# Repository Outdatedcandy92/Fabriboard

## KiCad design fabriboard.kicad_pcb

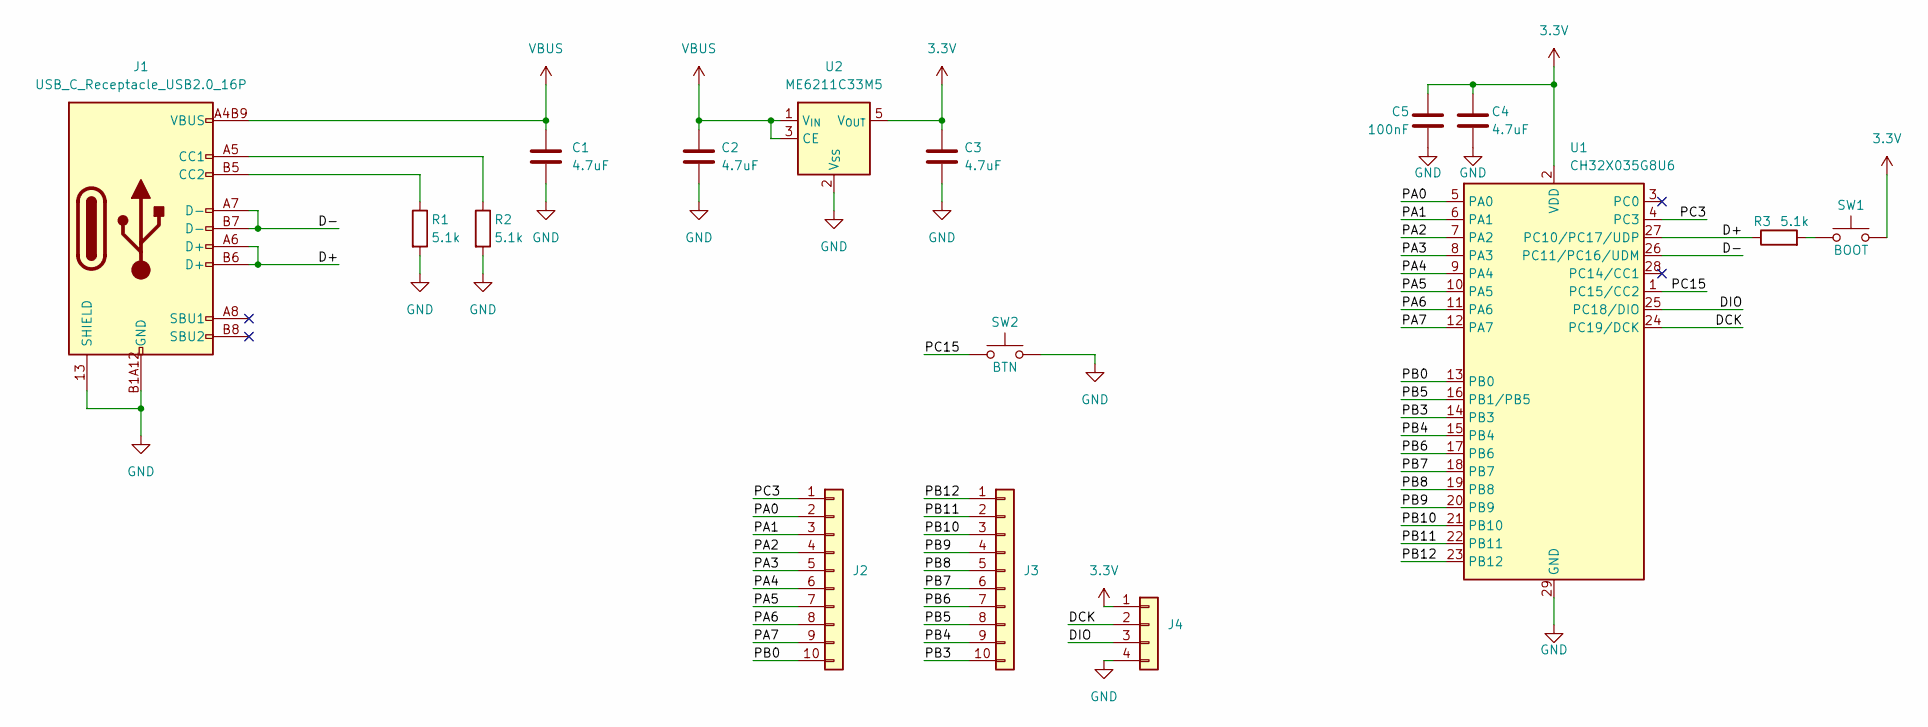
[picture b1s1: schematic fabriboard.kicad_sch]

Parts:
C1, C2, C3, C4: 4.7uF; C_0402_1005Metric
C5: 100nF; C_0402_1005Metric
J1: USB_C_Receptacle_USB2.0_16P; USB-C-SMD_TYPE-C-16PIN-2MD-073
J2, J3: Conn_01x10; PinHeader_1x10_P2.54mm_Vertical
J4: Conn_01x04; PinHeader_1x04_P2.54mm_Vertical
R1, R2, R3: 5.1k; R_0402_1005Metric
SW1: BOOT; SW-SMD_L3.9-W3.0-P4.45
SW2: BTN; SW-SMD_L3.9-W3.0-P4.45
U1: CH32X035G8U6; WQFN-28-1EP_4x4mm_P0.4mm_EP2.7x2.7mm
U2: ME6211C33M5; SOT-23-5

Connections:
3.3V: C3.1, C4.1, C5.1, J4.1, SW1.2, U1.2 (VDD), U2.5 (V_{OUT})
/D+: J1.A6 (D+), J1.B6 (D+), R3.1, U1.27 (PC10/PC17/UDP)
/D-: J1.A7 (D-), J1.B7 (D-), U1.26 (PC11/PC16/UDM)
/DCK: J4.2, U1.24 (PC19/DCK)
/DIO: J4.3, U1.25 (PC18/DIO)
/PA0: J2.2, U1.5 (PA0)
/PA1: J2.3, U1.6 (PA1)
/PA2: J2.4, U1.7 (PA2)
/PA3: J2.5, U1.8 (PA3)
/PA4: J2.6, U1.9 (PA4)
/PA5: J2.7, U1.10 (PA5)
/PA6: J2.8, U1.11 (PA6)
/PA7: J2.9, U1.12 (PA7)
/PB0: J2.10, U1.13 (PB0)
/PB3: J3.10, U1.14 (PB3)
/PB4: J3.9, U1.15 (PB4)
/PB5: J3.8, U1.16 (PB1/PB5)
/PB6: J3.7, U1.17 (PB6)
/PB7: J3.6, U1.18 (PB7)
/PB8: J3.5, U1.19 (PB8)
/PB9: J3.4, U1.20 (PB9)
/PB10: J3.3, U1.21 (PB10)
/PB11: J3.2, U1.22 (PB11)
/PB12: J3.1, U1.23 (PB12)
/PC3: J2.1, U1.4 (PC3)
/PC15: SW2.1, U1.1 (PC15/CC2)
GND: C1.2, C2.2, C3.2, C4.2, C5.2, J1.13 (SHIELD), J1.14 (SHIELD), J1.A1B12 (GND), J1.B1A12 (GND), J4.4, R1.2, R2.2, SW2.2, U1.29 (GND), U2.2 (V_{SS})
unnamed: J1.A5 (CC1), R2.1
unnamed: J1.B5 (CC2), R1.1
unnamed: R3.2, SW1.1
VBUS: C1.1, C2.1, J1.A4B9 (VBUS), J1.B4A9 (VBUS), U2.1 (V_{IN}), U2.3 (CE)

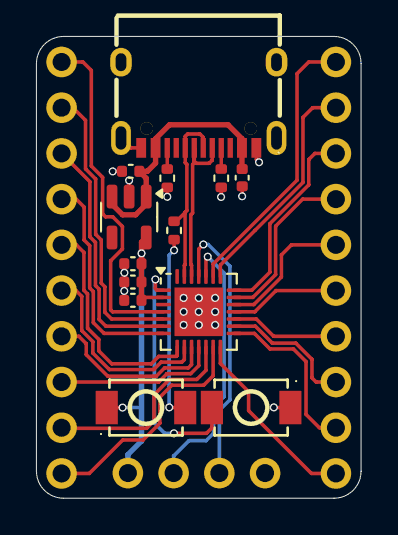
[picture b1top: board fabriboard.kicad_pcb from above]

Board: 2 copper layers, 18.0 x 25.7 mm, 16 parts (0 on the bottom side), 31 nets.
